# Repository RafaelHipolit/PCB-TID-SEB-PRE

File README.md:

# Projeto de PCB da IC: Instrumentação para o Estudo de Efeitos de Radiação em Dispositivos Eletrônicos

## Resumo da IC
O avanço da microeletrônica e a constante aplicação de dispositivos semicondutores em ambientes críticos, como os cenários aeroespaciais e nucleares, têm intensificado a necessidade de qualificar componentes eletrônicos quanto à sua tolerância à radiação ionizante. Nesse contexto, a caracterização precisa dos danos provocados exige instrumentação científica capaz de avaliar tanto os efeitos acumulativos, resultantes da Dose Ionizante Total (TID), quanto as falhas estocásticas provocadas por Efeitos de Evento Único (SEE). O presente trabalho teve como objetivo projetar e desenvolver uma plataforma eletrônica integrada, no formato de Placa de Circuito Impresso (PCB), dedicada ao estudo e à caracterização dos efeitos de radiação ionizante em transistores MOSFET de potência. 
        
O circuito implementado foi estruturado em três blocos funcionais distintos: um circuito para monitoramento de TID conectado à plataforma PXI, um circuito protetivo contra Efeitos de Queima por Sobrecorrente (SEB) baseado na Técnica de Limitação de Corrente e um circuito auxiliar de pré-amplificação focado na Espectroscopia de Carga.  Para viabilizar o uso dinâmico da plataforma sem a necessidade de reconfigurações manuais, a alternância de conexão entre os blocos operacionais e o Dispositivo Sob Teste (DUT) foi estabelecida por meio do chaveamento de relés de potência. O projeto elétrico, o layout das camadas e o modelo 3D da PCB foram desenvolvidos e validados computacionalmente no software KiCad, confirmando que a topologia concebida cumpre os requisitos de instrumentação.

---

# Metodologia

As técnicas de medição de efeitos de radiação em transistores, como a
Técnica de Limitação de Corrente e Técnica de Espectroscopia de Carga,
necessitam de componentes e equipamentos que existem comercialmente e
são comumente encontradas em laboratórios de física nuclear. Entretanto,
devido à grande variedade de dispositivos eletrônicos necessários para
implementar as diferentes técnicas, não existe uma solução comercial
viável de propósito geral para qualificação de transistores sob efeitos
de radiação. Assim, percebe-se uma necessidade de desenvolver uma
plataforma integrada de testes suficientemente geral que atenda
simultaneamente às exigências específicas de ensaios de efeitos
estocásticos e acumulativos de radiação para uma ampla gama de
transistores.

Tendo esse contexto em mente, este projeto de pesquisa visa projetar uma
plataforma integrada, na forma de placa de circuito impresso (PCB -
*Printed Circuit Board*) que auxilie o estudo e caracterização dos
efeitos de radiação ionizante em dispositivos eletrônicos. A PCB a ser
elaborada deve focar em TID para efeitos acumulativos e SEE para efeitos
estocásticos. Para medição de SEE deve-se utilizar a Técnica de
Limitação de Corrente e Técnica de Espectroscopia de Carga.

O circuito projetado na PCB deve ser dividido em três blocos: Circuito
TID, Circuito SEB e Circuito Pré-Amplificador. Os três circuitos devem
ser integrados de forma que apenas um esteja conectado ao DUT por vez e
que a troca do circuito conectado ao DUT possa ser realizada
dinamicamente.

## Circuito TID

Esse circuito deve auxiliar na medição do efeito de TID. Para isso ele
deve conectar os terminais do DUT a uma SMU para monitoramento de
parâmetros do dispositivo. No caso desse projeto, a SMU será por meio da
plataforma modular PXI (*PCI eXtensions for Instrumentation*). Portanto,
a saída deste circuito deve obedecer a padronização de conexão com a
plataforma PXI. Tal padrão consiste de nove eletrodos de controle e
automação, que obedece o seguinte ordenamento sequencial:

-   Eletrodo positivo de porta (POS G).

-   Eletrodo negativo de porta (NEG G).

-   Eletrodo positivo de dreno (POS D).

-   Eletrodo negativo de dreno (NED G).

-   Eletrodo negativo de sensoriamento de dreno (NEG SD).

-   Eletrodo positivo de sensoriamento de dreno (POS SD).

-   Fonte DC (+5 V).

-   Fonte DC (+5 V).

-   Fonte DC (+5 V).

Em nosso contexto, os últimos três terminais de fonte DC +5 V são
utilizados para controle automatizado de relês de alta tensão.

## Circuito SEB

O Circuito SEB deve auxiliar a medição do Efeito Único de Queima por
Sobrecorrente. Para isso, ele deve implementar a Técnica de Limitação de
Corrente com um arranjo de resistores de proteção. A saída do circuito
deve disponibiliza os sinais transientes do DUT para instrumentos
externos de aquisição. O terminal de saída desse circuito deve possuir
impedância de 50para evitar reflexões em sistemas de aquisição
ultra-rápidos. Além disso, o sistema protetivo deve possibilitar a
seleção do resistor de proteção apropriado (10 k- 1 M) ao DUT, de forma
a assegurar a eficácia da técnica de limitação de corrente.

## Circuito Pré-Amplificador

O Circuito Pré-Amplificador deve auxiliar o arranjo da Técnica de
Espectroscopia de Carga por meio da implementação do Pré-Amplificador
Sensível à Carga presente nesta técnica. Sua saída deve apresentar
impedância de 50 ohms para casamento com sistemas de aquisição
ultra-rápidos. Para definir o ganho nominal de pré-amplificação de
aproximadamente 45 mV/MeV em sensores de silício, um capacitor de
retroalimentação de 1 pF foi escolhido. Para possibilitar a
discriminação de eventos distintos induzidos por partículas ionizantes a
taxas médias inferiores a $2 \times 10^{6}$ eventos/s, tipicamente
adotadas em testes dedicados com aceleradores de partículas, um resistor
de retroalimentação de 100 kfoi considerado.

## Integração dos circuitos

Os três circuitos devem ser integrados de forma que apenas um esteja
conectado ao DUT por vez. Para realizar essa alternância de conexão deve
ser utilizados relés de potência para conectar apenas um dos circuitos
por vez ao DUT. O controle desses relés deve ser por meio plataforma
PXI, utilizando a conexão implementada no Circuito TID.

## Conexão com o transistor DUT

Visando o propósito generalista da plataforma integrada de testes e
buscando maior praticidade na substituição de diferentes DUTs na
instrumentação proposta, optou-se por realizar a conexão entre o DUT e o
sistema por meio do acoplamento entre uma PCB-mãe (sistema) e uma
PCB-filha (DUT), através de barras de pinos torneados. A PCB-filha deve
passar os sinais de porta, dreno e fonte. O uso dessa arquitetura
modular justifica-se por sua disponibilidade prévia no Laboratório onde
este projeto é realizado, facilitando o uso de diferentes transistores
na PCB elaborada neste projeto.

# Resultados

Este capítulo descreve o projeto de PCB elaborada para atender ao
objetivos do presente trabalho.

## Esquemático da PCB

A Figura mostra o esquemático da PCB
elaborada no software KiCad.

![Esquemático da
PCB.](images/circuitoABC_schematic.jpg)

Esquemático da PCB.

Esquemático da
PCB.

### Configuração da interface PXI

Os 9 pinos que se conectam à interface PXI seguem a estrutura na PCB:

-   POS G: sinal de tensão do *gate-source* do transistor.

-   NEG G: sinal de terra.

-   POS D: sinal de tensão do *drain-source* do transistor.

-   NEG D: sinal de terra.

-   NEG SD: sinal de terra.

-   POS SD: sinal de tensão do *drain-source* do transistor.

-   +5V RELAY1: ativa o relé 1 com 5V.

-   +5V RELAY2: ativa o relé 2 com 5V.

-   +5V RELAY3: ativa o relé 3 com 5V.

### Arranjo de resistores de proteção

No circuito SEB, devido a diferentes possíveis necessidades de valor
para o resistor de proteção empregado na Técnica de Limitação de
Corrente, foi elaborado um arranjo de resistores de proteção. Neste
arranjo há espaço para 9 resistores de proteção.

A conexão do resistor RP1 ou dos demais resistores pode ser alterada
dinamicamente utilizando o relé 3. Os resistores RP2 até RP9 estão
conectados em paralelo, porém cada um pode ser desconectado manualmente
utilizando um jumper. Ademais, uma trilha para conexão sem resistor de
proteção está presente.

### Configuração dos relés

Foram utilizados 3 relés duplos, ou seja, 3 circuitos integrados nos
quais cada um contém 2 relés que são ativados simultaneamente. Os relés
1 e 2 realizam a troca de conexão dos circuitos com o DUT. O relé 3
realiza a troca de resistor de proteção dinamicamente. A tabela descreve
a configuração de cada relé.

| -------- |--------------------- |---------------------------------|    
| -------- |--------------------- |---------------------------------|                                
| Relé 1   |Normalmente Aberto    |Conecta o porta e dreno do DUT ao Circuito TID|                              
|         |Normalmente Fechado   |Conecta o porta e dreno do DUT ao Circuito SEB ou Pré-Amp.|
| -------- |--------------------- |--------------------------------|
| Relé 2   |Normalmente Aberto    |Conecta o porta e dreno do DUT ao Circuito Pré-Amplificador     |                          
|         |Normalmente Fechado   |Conecta o porta e dreno do DUT ao Circuito SEB|
| -------- |--------------------- |--------------------------------|
| Relé 3   |Normalmente Aberto    |Utiliza o resistores RP2 a RP9 como resistor de proteção     |                         
|         |Normalmente Fechado   |Utiliza o resistor RP1 como resistor de proteção|
| -------- |--------------------- |--------------------------------|

Configuração de cada relé.

## Layout da PCB

A Figura mostra o layout da PCB elaborada no
software KiCad. Na esquerda da PCB se encontra o Circuito SEB e Circuito
TID. Na borda da placa, encontram-se os conectores dos sinais de entrada
e saída do Circuito SEB. Em seguida é visível o arranjo de resistores de
proteção, os 3 relés e os pinos para conexão do Circuito TID com a
plataforma PXI. No centro da PCB encontram-se os pinos para conexão com
a PCB-filha e, portanto, conexão com o DUT. Na direita da PCB há o
Circuito Pré-Amplificador.

Layout da camada inferior da PCB.

Layout da camada superior da PCB

A Figura mostra o modelo 3D da PCB no software
KiCad, no qual é possível visualizar todos os componentes da placa e as
legendas impressas na camada de serigrafia (*silkscreen*) dos conectores
de entrada e saída dos sinais.

![Modelo 3D da PCB no software KiCad. Visualização da camada
inferior.](images/circuitoABC_3d.png)

Modelo 3D da PCB no software KiCad. Visualização da camada
inferior.

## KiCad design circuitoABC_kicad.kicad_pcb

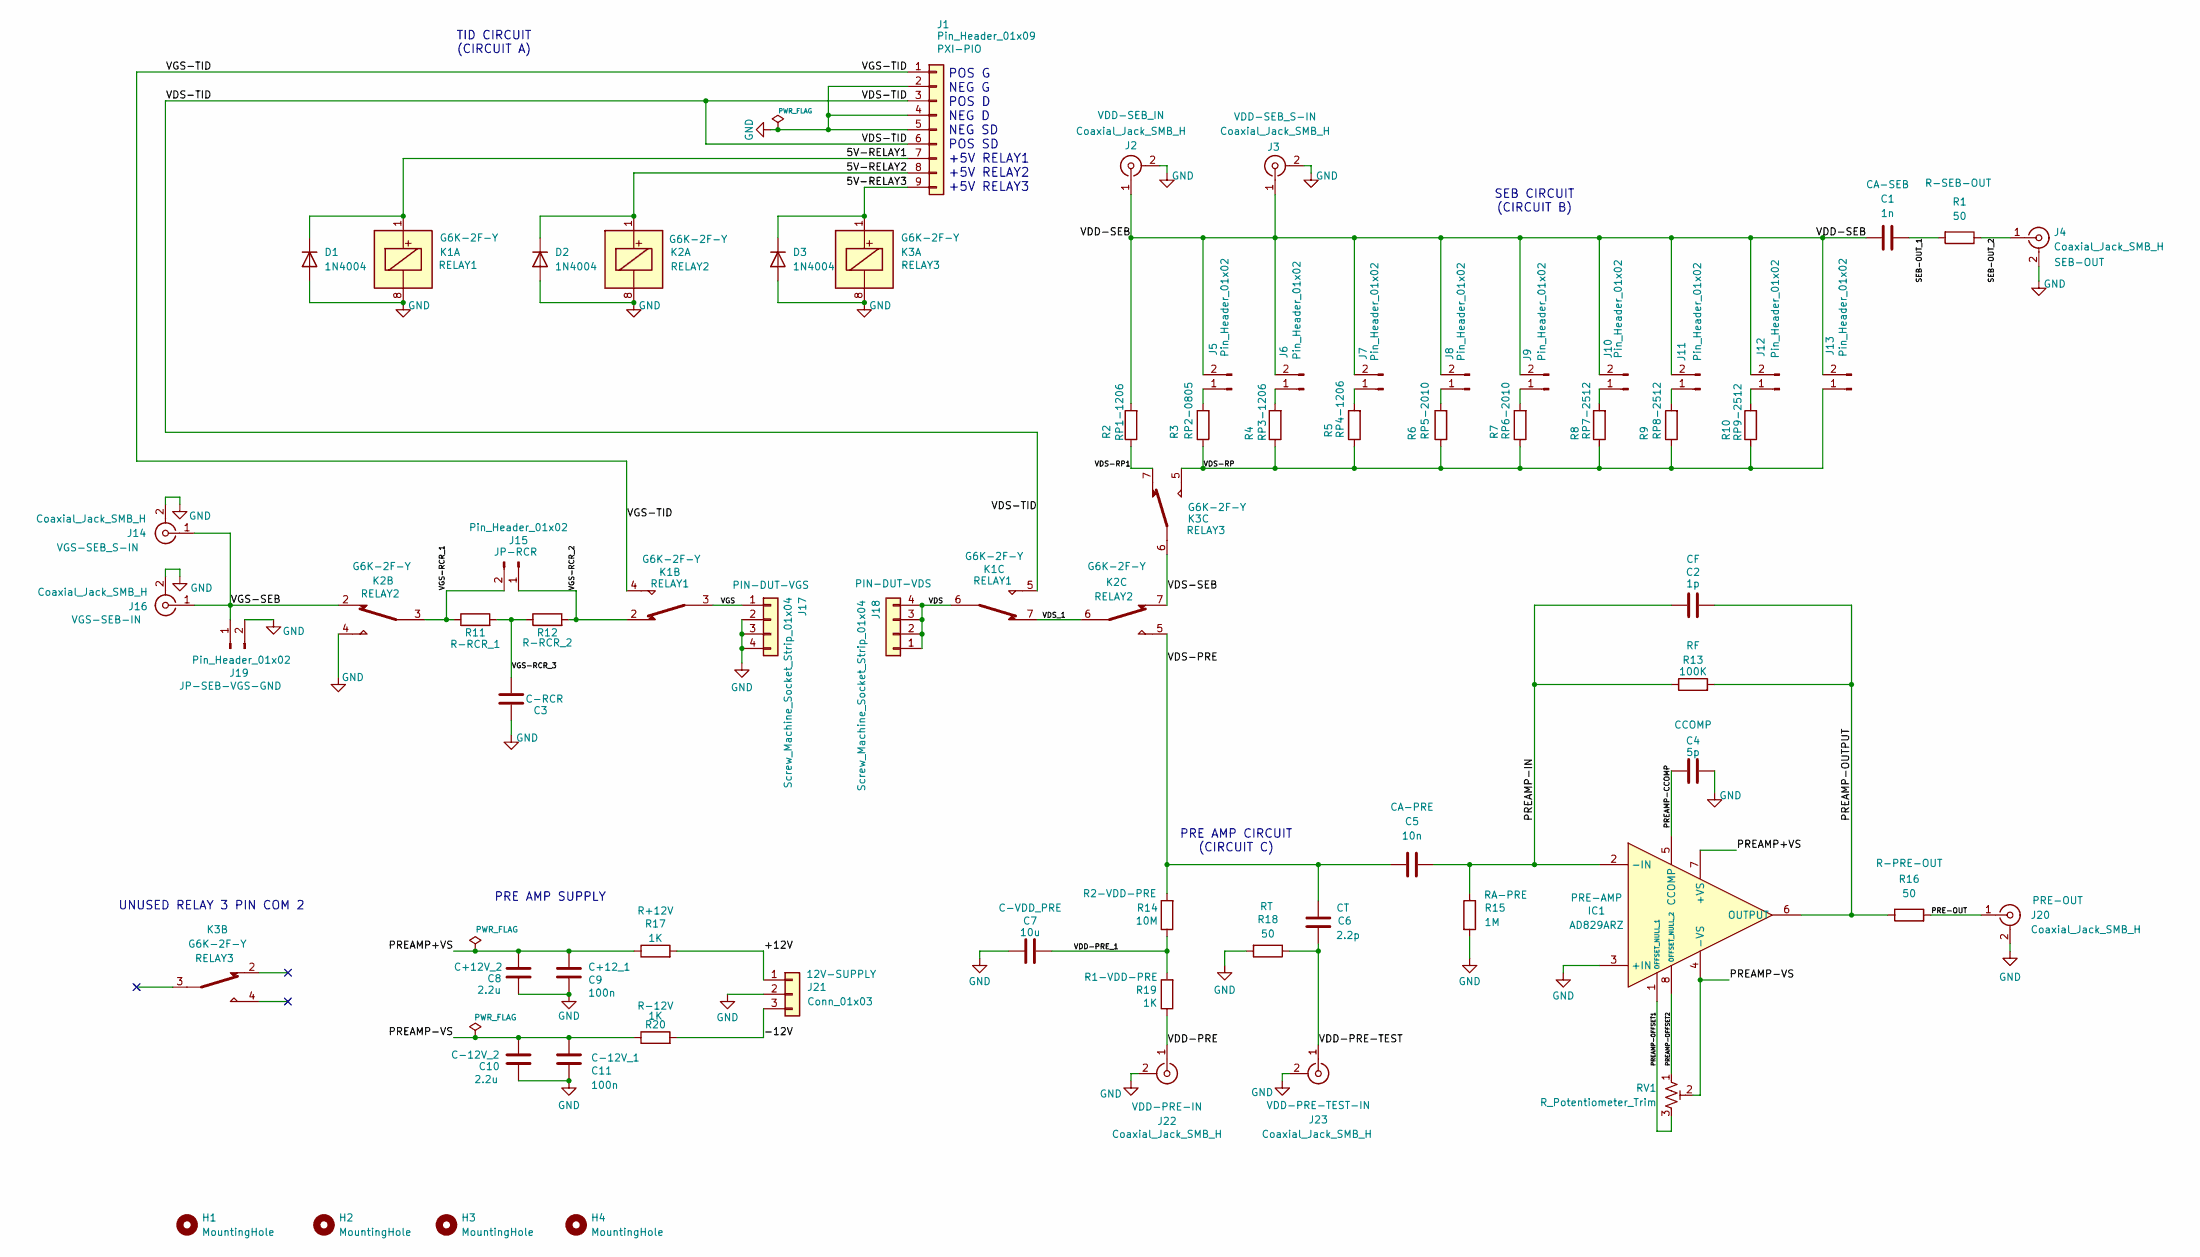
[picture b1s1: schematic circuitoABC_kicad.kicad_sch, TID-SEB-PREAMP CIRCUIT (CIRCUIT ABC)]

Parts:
C1: 1n; C_0805_2012Metric
C2: 1p; C_0805_2012Metric
C3: C_0805_2012Metric
C4: 5p; C_0805_2012Metric
C5: 10n; C_0805_2012Metric
C6: 2.2p; C_0805_2012Metric
C7: 10u; C_0805_2012Metric
C8, C10: 2.2u; C_0805_2012Metric
C9, C11: 100n; C_0805_2012Metric
D1, D2, D3: 1N4004; D_DO-41_SOD81_P10.16mm_Horizontal
H1, H2, H3, H4: MountingHole; MountingHole_3.2mm_M3
IC1: AD829ARZ; SOIC127P600X175-8N; Manufacturer_Part_Number AD829ARZ; Mouser Part Number 584-AD829ARZ
J1: Pin_Header_01x09; PinHeader_1x09_P2.54mm_Vertical
J2, J3, J4, J14, J16, J20, J22, J23: Coaxial_Jack_SMB_H; 731000103
J5, J6, J7, J8, J9, J10, J11, J12, J13, J15, J19: Pin_Header_01x02; PinHeader_1x02_P2.54mm_Vertical
J17, J18: Screw_Machine_Socket_Strip_01x04; PinSocket_1x04_P2.54mm_Vertical
J21: Conn_01x03; PhoenixContact_MSTBA_2,5_3-G_1x03_P5.00mm_Horizontal
K1, K2, K3: G6K-2F-Y; Relay_DPDT_Omron_G6K-2F-Y
R1, R16, R18: 50; R_0805_2012Metric
R2, R4, R5: R_1206_3216Metric
R3, R11, R12: R_0805_2012Metric
R6, R7: R_2010_5025Metric
R8, R9, R10: R_2512_6332Metric
R13: 100K; R_0805_2012Metric
R14: 10M; R_0805_2012Metric
R15: 1M; R_0805_2012Metric
R17, R19, R20: 1K; R_0805_2012Metric
RV1: R_Potentiometer_Trim; Potentiometer_Bourns_3296W_Vertical

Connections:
/5V-RELAY1: D1.1 (K), J1.7, K1.1
/5V-RELAY2: D2.1 (K), J1.8, K2.1
/5V-RELAY3: D3.1 (K), J1.9, K3.1
/+12V: J21.1, R17.2
/-12V: J21.3, R20.2
/PRE-OUT: J20.1 (In), R16.2
/PREAMP+VS: C8.2, C9.2, IC1.7 (+VS), R17.1
/PREAMP-CCOMP: C4.2, IC1.5 (CCOMP)
/PREAMP-IN: C2.1, C5.2, IC1.2 (-IN), R13.1, R15.1
/PREAMP-OFFSET1: IC1.1 (OFFSET_NULL_1), RV1.3
/PREAMP-OFFSET2: IC1.8 (OFFSET_NULL_2), RV1.1
/PREAMP-OUTPUT: C2.2, IC1.6 (OUTPUT), R13.2, R16.1
/PREAMP-VS: C10.2, C11.2, IC1.4 (-VS), R20.1, RV1.2
/SEB-OUT_1: C1.2, R1.2
/SEB-OUT_2: J4.1 (In), R1.1
/VDD-PRE: J22.1 (In), R19.1
/VDD-PRE-TEST: C6.1, J23.1 (In), R18.1
/VDD-PRE_1: C7.2, R14.1, R19.2
/VDD-SEB: C1.1, J2.1 (In), J3.1 (In), J5.2, J6.2, J7.2, J8.2, J9.2, J10.2, J11.2, J12.2, J13.2, R2.2
/VDS: J18.1, J18.2, J18.3, J18.4, K1.6
/VDS-PRE: C5.1, C6.2, K2.5, R14.2
/VDS-RP: J13.1, K3.5, R3.1, R4.1, R5.1, R6.1, R7.1, R8.1, R9.1, R10.1
/VDS-RP1: K3.7, R2.1
/VDS-SEB: K2.7, K3.6
/VDS-TID: J1.3, J1.6, K1.5
/VDS_1: K1.7, K2.6
/VGS: J17.1, K1.3
/VGS-RCR_1: J15.2, K2.3, R11.1
/VGS-RCR_2: J15.1, K1.2, R12.2
/VGS-RCR_3: C3.1, R11.2, R12.1
/VGS-SEB: J14.1 (In), J16.1 (In), J19.1, K2.2
/VGS-TID: J1.1, K1.4
GND: C3.2, C4.1, C7.1, C8.1, C9.1, C10.1, C11.1, D1.2 (A), D2.2 (A), D3.2 (A), IC1.3 (+IN), J1.2, J1.4, J1.5, J2.2 (Ext), J3.2 (Ext), J4.2 (Ext), J14.2 (Ext), J16.2 (Ext), J17.2, J17.3, J17.4, J19.2, J20.2 (Ext), J21.2, J22.2 (Ext), J23.2 (Ext), K1.8, K2.4, K2.8, K3.8, R15.2, R18.2
unnamed: J5.1, R3.2
unnamed: J6.1, R4.2
unnamed: J7.1, R5.2
unnamed: J8.1, R6.2
unnamed: J9.1, R7.2
unnamed: J10.1, R8.2
unnamed: J11.1, R9.2
unnamed: J12.1, R10.2

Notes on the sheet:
PRE AMP CIRCUIT (CIRCUIT C)
PRE AMP SUPPLY
UNUSED RELAY 3 PIN COM 2
POS G NEG G POS D NEG D NEG SD POS SD +5V RELAY1 +5V RELAY2 +5V RELAY3
TID CIRCUIT (CIRCUIT A)
SEB CIRCUIT (CIRCUIT B)

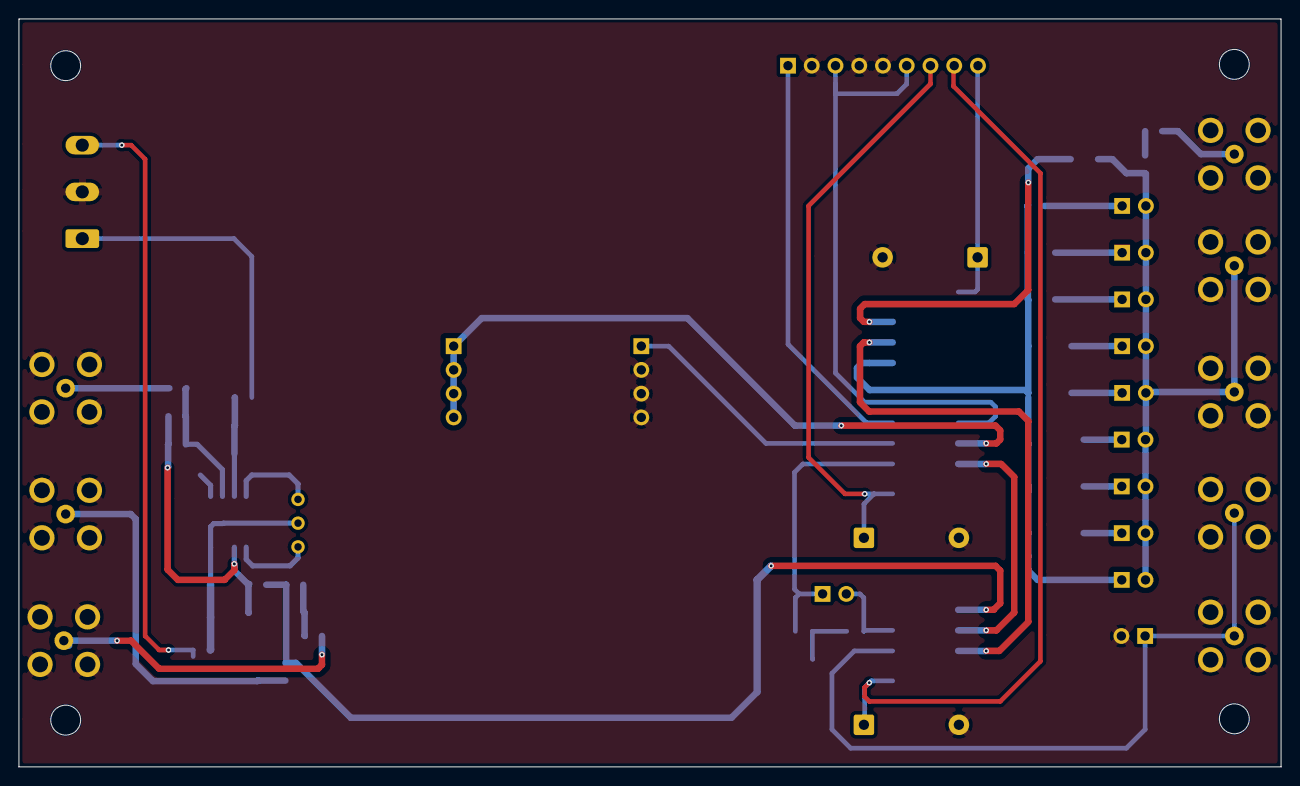
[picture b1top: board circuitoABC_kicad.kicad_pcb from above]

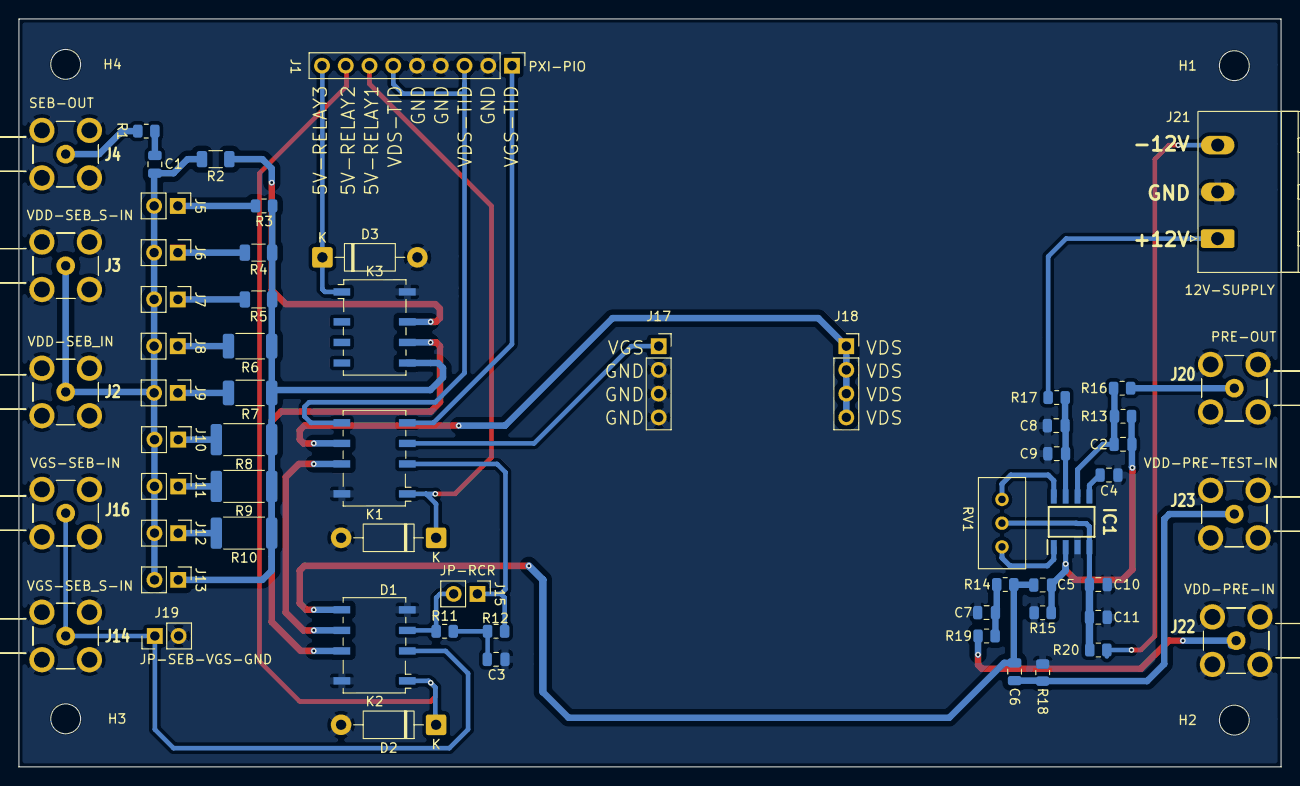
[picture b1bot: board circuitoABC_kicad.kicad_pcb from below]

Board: 2 copper layers, 135.0 x 80.0 mm, 66 parts (66 on the bottom side), 41 nets.
